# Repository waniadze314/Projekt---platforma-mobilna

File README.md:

# Projekt---platforma-mobilna
Projekt zespołowy

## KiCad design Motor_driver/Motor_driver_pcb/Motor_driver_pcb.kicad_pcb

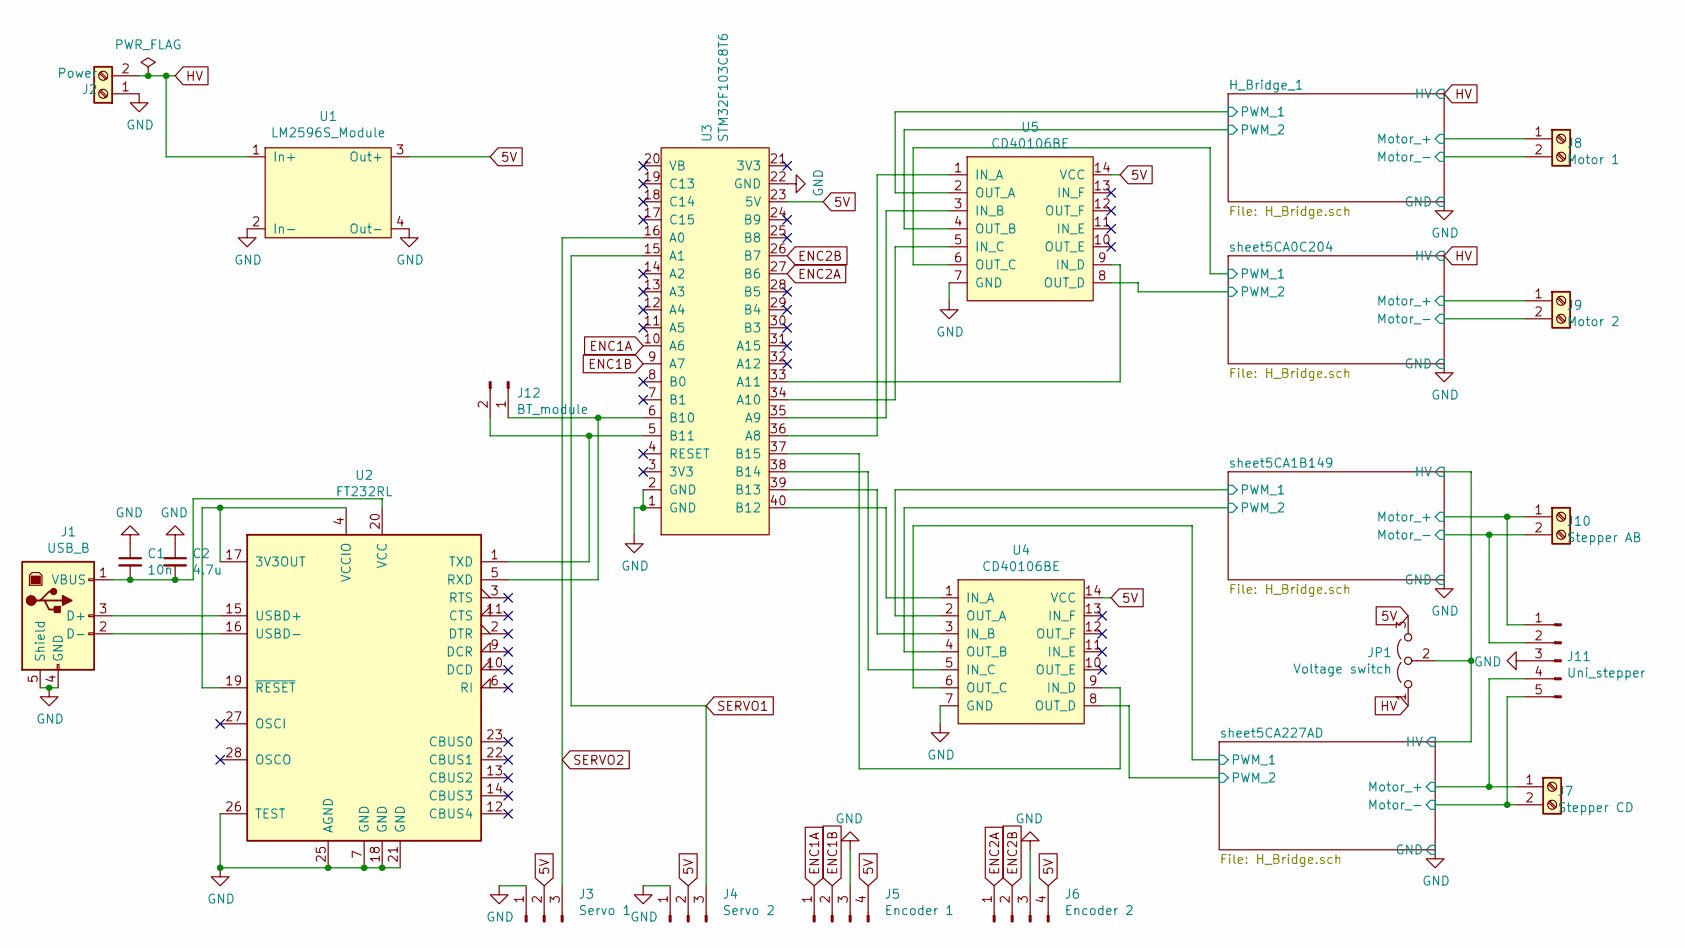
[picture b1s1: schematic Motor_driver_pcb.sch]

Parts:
C1: 10n; C_0805_2012Metric_Pad1.15x1.40mm_HandSolder
C2: 4.7u; CP_Radial_D5.0mm_P2.00mm
J1: USB_B; USB_B_OST_USB-B1HSxx_Horizontal
J2: Power; PinSocket_1x02_P2.54mm_Vertical
J3: Servo 1; PinHeader_1x03_P2.54mm_Vertical
J4: Servo 2; PinHeader_1x03_P2.54mm_Vertical
J5: Encoder 1; PinHeader_1x04_P2.54mm_Vertical
J6: Encoder 2; PinHeader_1x04_P2.54mm_Vertical
J7: Stepper CD; PinSocket_1x02_P2.54mm_Vertical
J8: Motor 1; PinSocket_1x02_P2.54mm_Vertical
J9: Motor 2; PinSocket_1x02_P2.54mm_Vertical
J10: Stepper AB; PinSocket_1x02_P2.54mm_Vertical
J11: Uni_stepper; PinHeader_1x05_P2.54mm_Vertical
J12: BT_module; PinHeader_1x02_P2.54mm_Vertical
JP1: Voltage switch; PinHeader_1x03_P2.54mm_Vertical
U1: LM2596S_Module; LM2596_Module
U2: FT232RL; SSOP-28_5.3x10.2mm_P0.65mm
U3: STM32F103C8T6; STM32F103C8T6_Board
U4, U5: CD40106BE; DIP-14_W7.62mm

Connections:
5V: J3.2, J4.2, J5.4, J6.4, JP1.3 (B), U1.3 (Out+), U3.23 (5V), U4.14 (VCC), U5.14 (VCC)
/H_Bridge_1/Motor_+: J8.1; also elsewhere on the board
/H_Bridge_1/Motor_-: J8.2; also elsewhere on the board
/H_Bridge_1/PWM_1: U5.2 (OUT_A); also elsewhere on the board
/H_Bridge_1/PWM_2: U5.4 (OUT_B); also elsewhere on the board
/sheet5CA0C204/Motor_+: J9.1; also elsewhere on the board
/sheet5CA0C204/Motor_-: J9.2; also elsewhere on the board
/sheet5CA0C204/PWM_1: U5.6 (OUT_C); also elsewhere on the board
/sheet5CA0C204/PWM_2: U5.8 (OUT_D); also elsewhere on the board
/sheet5CA1B149/HV: JP1.2 (C); also elsewhere on the board
/sheet5CA1B149/Motor_+: J10.1, J11.1; also elsewhere on the board
/sheet5CA1B149/Motor_-: J10.2, J11.2; also elsewhere on the board
/sheet5CA1B149/PWM_1: U4.2 (OUT_A); also elsewhere on the board
/sheet5CA1B149/PWM_2: U4.4 (OUT_B); also elsewhere on the board
/sheet5CA227AD/Motor_+: J7.1, J11.4; also elsewhere on the board
/sheet5CA227AD/Motor_-: J7.2, J11.5; also elsewhere on the board
/sheet5CA227AD/PWM_1: U4.6 (OUT_C); also elsewhere on the board
/sheet5CA227AD/PWM_2: U4.8 (OUT_D); also elsewhere on the board
ENC1A: J5.1, U3.10 (A6)
ENC1B: J5.2, U3.9 (A7)
ENC2A: J6.1, U3.27 (B6)
ENC2B: J6.2, U3.26 (B7)
GND: C1.1, C2.1, J1.4 (GND), J1.5 (Shield), J2.1, J3.1, J4.1, J5.3, J6.3, J11.3, U1.2 (In-), U1.4 (Out-), U2.7 (GND), U2.18 (GND), U2.21 (GND), U2.25 (AGND), U2.26 (TEST), U3.1 (GND), U3.2 (GND), U3.22 (GND), U4.7 (GND), U5.7 (GND); also elsewhere on the board
HV: J2.2, JP1.1 (A), U1.1 (In+); also elsewhere on the board
unnamed: C1.2, C2.2, J1.1 (VBUS), U2.20 (VCC)
unnamed: J1.2 (D-), U2.16 (USBD-)
unnamed: J1.3 (D+), U2.15 (USBD+)
unnamed: J12.1, U2.5 (RXD), U3.6 (B10)
unnamed: J12.2, U2.1 (TXD), U3.5 (B11)
unnamed: U2.4 (VCCIO), U2.17 (3V3OUT), U2.19 (~RESET~)
unnamed: U3.33 (A11), U5.9 (IN_D)
unnamed: U3.34 (A10), U5.5 (IN_C)
unnamed: U3.35 (A9), U5.3 (IN_B)
unnamed: U3.36 (A8), U5.1 (IN_A)
unnamed: U3.37 (B15), U4.9 (IN_D)
unnamed: U3.38 (B14), U4.5 (IN_C)
unnamed: U3.39 (B13), U4.3 (IN_B)
unnamed: U3.40 (B12), U4.1 (IN_A)
SERVO1: J4.3, U3.15 (A1)
SERVO2: J3.3, U3.16 (A0)

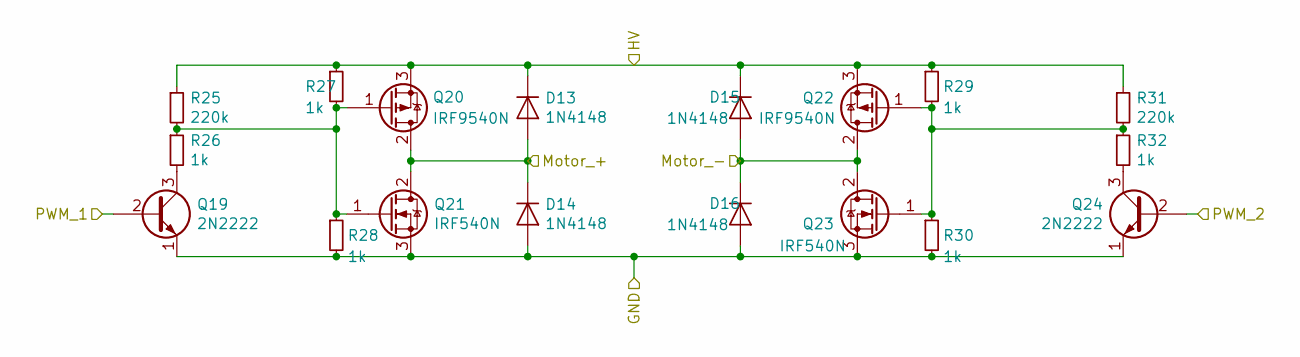
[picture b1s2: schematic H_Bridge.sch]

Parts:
D1, D2, D3, D4: 1N4148; D_DO-35_SOD27_P7.62mm_Horizontal
Q1, Q6: 2N2222; TO-92
Q2, Q4: IRF9540N; TO-220-3_Vertical
Q3, Q5: IRF540N; TO-220-3_Vertical
R1, R7: 220k; R_0805_2012Metric_Pad1.15x1.40mm_HandSolder
R2, R3, R4, R5, R6, R8: 1k; R_0805_2012Metric_Pad1.15x1.40mm_HandSolder

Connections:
/H_Bridge_1/Motor_+: D1.2 (A), D2.1 (K), Q2.2 (D), Q3.2 (D); also elsewhere on the board
/H_Bridge_1/Motor_-: D3.2 (A), D4.1 (K), Q4.2 (D), Q5.2 (D); also elsewhere on the board
/H_Bridge_1/PWM_1: Q1.2 (B); also elsewhere on the board
/H_Bridge_1/PWM_2: Q6.2 (B); also elsewhere on the board
GND: D2.2 (A), D4.2 (A), Q1.1 (E), Q3.3 (S), Q5.3 (S), Q6.1 (E), R4.2, R6.2; also elsewhere on the board
HV: D1.1 (K), D3.1 (K), Q2.3 (S), Q4.3 (S), R1.1, R3.1, R5.1, R7.1; also elsewhere on the board
unnamed: Q1.3 (C), R2.2
unnamed: Q2.1 (G), Q3.1 (G), R1.2, R2.1, R3.2, R4.1
unnamed: Q4.1 (G), Q5.1 (G), R5.2, R6.1, R7.2, R8.1
unnamed: Q6.3 (C), R8.2

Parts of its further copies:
D5, D6, D7, D8, D9, D10, D11, D12, D13, D14, D15, D16: 1N4148; D_DO-35_SOD27_P7.62mm_Horizontal
Q7, Q12, Q13, Q18, Q19, Q24: 2N2222; TO-92
Q8, Q10, Q14, Q16, Q20, Q22: IRF9540N; TO-220-3_Vertical
Q9, Q11, Q15, Q17, Q21, Q23: IRF540N; TO-220-3_Vertical
R9, R15, R17, R23, R25, R31: 220k; R_0805_2012Metric_Pad1.15x1.40mm_HandSolder
R10, R11, R12, R13, R14, R16, R18, R19, R20, R21, R22, R24, R26, R27, R28, R29, R30, R32: 1k; R_0805_2012Metric_Pad1.15x1.40mm_HandSolder

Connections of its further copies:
/sheet5CA0C204/Motor_+: D5.2 (A), D6.1 (K), Q8.2 (D), Q9.2 (D); also elsewhere on the board
/sheet5CA0C204/Motor_-: D7.2 (A), D8.1 (K), Q10.2 (D), Q11.2 (D); also elsewhere on the board
/sheet5CA0C204/PWM_1: Q7.2 (B); also elsewhere on the board
/sheet5CA0C204/PWM_2: Q12.2 (B); also elsewhere on the board
/sheet5CA1B149/HV: D9.1 (K), D11.1 (K), D13.1 (K), D15.1 (K), Q14.3 (S), Q16.3 (S), Q20.3 (S), Q22.3 (S), R17.1, R19.1, R21.1, R23.1, R25.1, R27.1, R29.1, R31.1; also elsewhere on the board
/sheet5CA1B149/Motor_+: D9.2 (A), D10.1 (K), Q14.2 (D), Q15.2 (D); also elsewhere on the board
/sheet5CA1B149/Motor_-: D11.2 (A), D12.1 (K), Q16.2 (D), Q17.2 (D); also elsewhere on the board
/sheet5CA1B149/PWM_1: Q13.2 (B); also elsewhere on the board
/sheet5CA1B149/PWM_2: Q18.2 (B); also elsewhere on the board
/sheet5CA227AD/Motor_+: D13.2 (A), D14.1 (K), Q20.2 (D), Q21.2 (D); also elsewhere on the board
/sheet5CA227AD/Motor_-: D15.2 (A), D16.1 (K), Q22.2 (D), Q23.2 (D); also elsewhere on the board
/sheet5CA227AD/PWM_1: Q19.2 (B); also elsewhere on the board
/sheet5CA227AD/PWM_2: Q24.2 (B); also elsewhere on the board
GND: D6.2 (A), D8.2 (A), D10.2 (A), D12.2 (A), D14.2 (A), D16.2 (A), Q7.1 (E), Q9.3 (S), Q11.3 (S), Q12.1 (E), Q13.1 (E), Q15.3 (S), Q17.3 (S), Q18.1 (E), Q19.1 (E), Q21.3 (S), Q23.3 (S), Q24.1 (E), R12.2, R14.2, R20.2, R22.2, R28.2, R30.2; also elsewhere on the board
HV: D5.1 (K), D7.1 (K), Q8.3 (S), Q10.3 (S), R9.1, R11.1, R13.1, R15.1; also elsewhere on the board
unnamed: Q7.3 (C), R10.2
unnamed: Q8.1 (G), Q9.1 (G), R9.2, R10.1, R11.2, R12.1
unnamed: Q10.1 (G), Q11.1 (G), R13.2, R14.1, R15.2, R16.1
unnamed: Q12.3 (C), R16.2
unnamed: Q13.3 (C), R18.2
unnamed: Q14.1 (G), Q15.1 (G), R17.2, R18.1, R19.2, R20.1
unnamed: Q16.1 (G), Q17.1 (G), R21.2, R22.1, R23.2, R24.1
unnamed: Q18.3 (C), R24.2
unnamed: Q19.3 (C), R26.2
unnamed: Q20.1 (G), Q21.1 (G), R25.2, R26.1, R27.2, R28.1
unnamed: Q22.1 (G), Q23.1 (G), R29.2, R30.1, R31.2, R32.1
unnamed: Q24.3 (C), R32.2

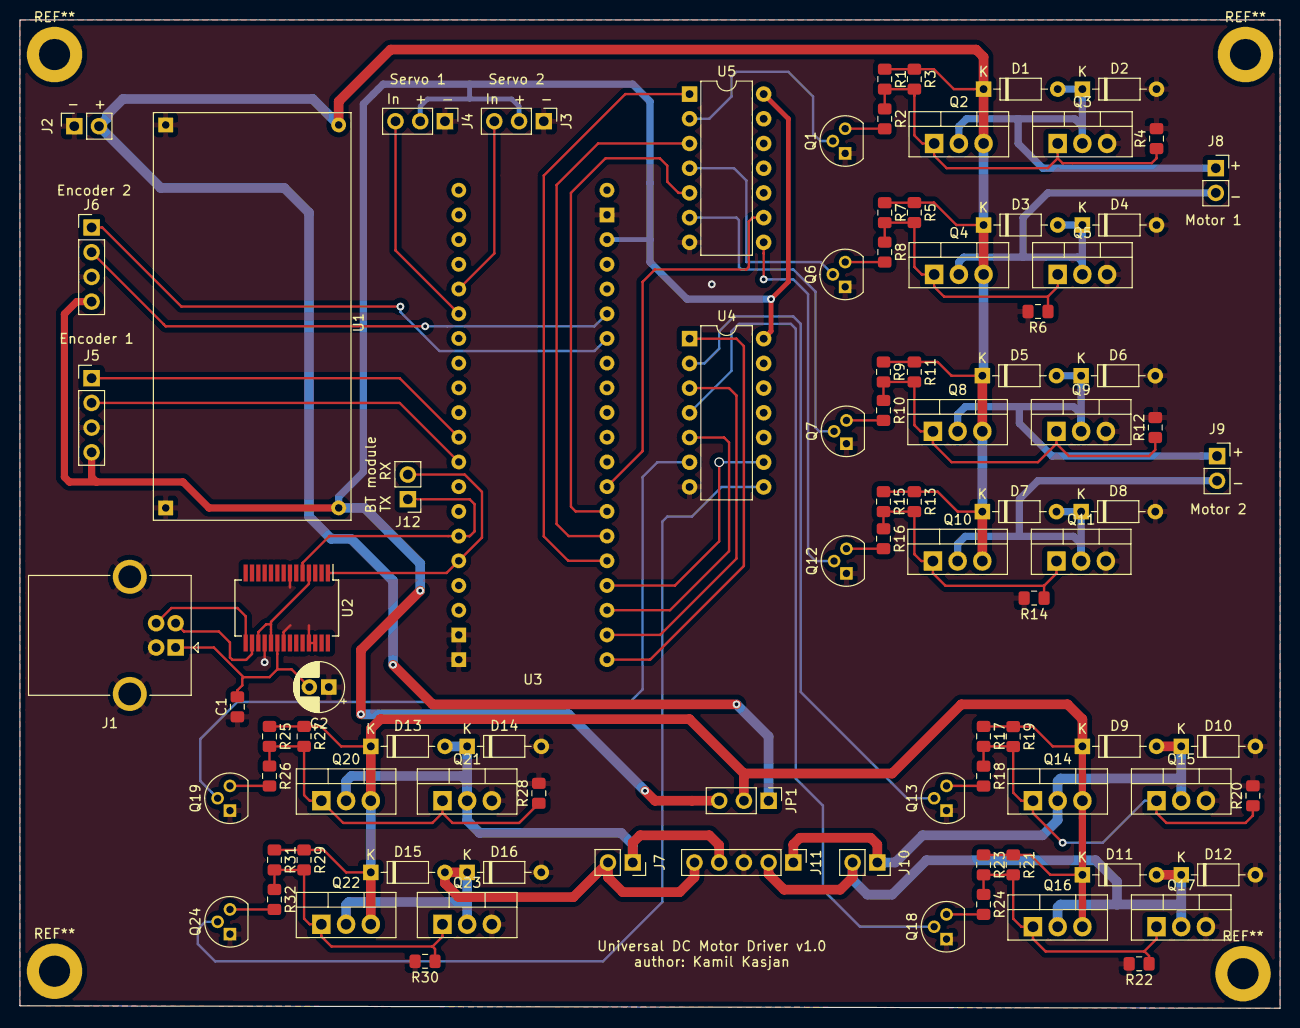
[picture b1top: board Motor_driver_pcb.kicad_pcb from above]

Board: 2 copper layers, 129.5 x 101.6 mm, 92 parts (0 on the bottom side), 56 nets.

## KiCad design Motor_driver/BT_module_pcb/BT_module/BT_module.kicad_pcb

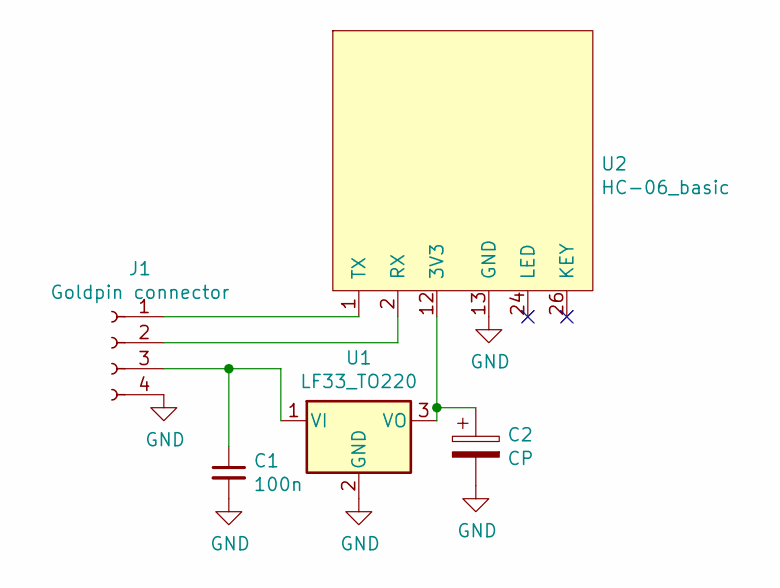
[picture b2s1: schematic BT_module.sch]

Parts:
C1: 100n; C_0805_2012Metric_Pad1.15x1.40mm_HandSolder
C2: CP; CP_Radial_D4.0mm_P2.00mm
J1: Goldpin connector; PinSocket_1x04_P2.54mm_Vertical
U1: LF33_TO220; TO-220-3_Vertical
U2: HC-06_basic; HC-05

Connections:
GND: C1.2, C2.2, J1.4, U1.2 (GND), U2.13 (GND)
unnamed: C1.1, J1.3, U1.1 (VI)
unnamed: C2.1, U1.3 (VO), U2.12 (3V3)
unnamed: J1.1, U2.1 (TX)
unnamed: J1.2, U2.2 (RX)

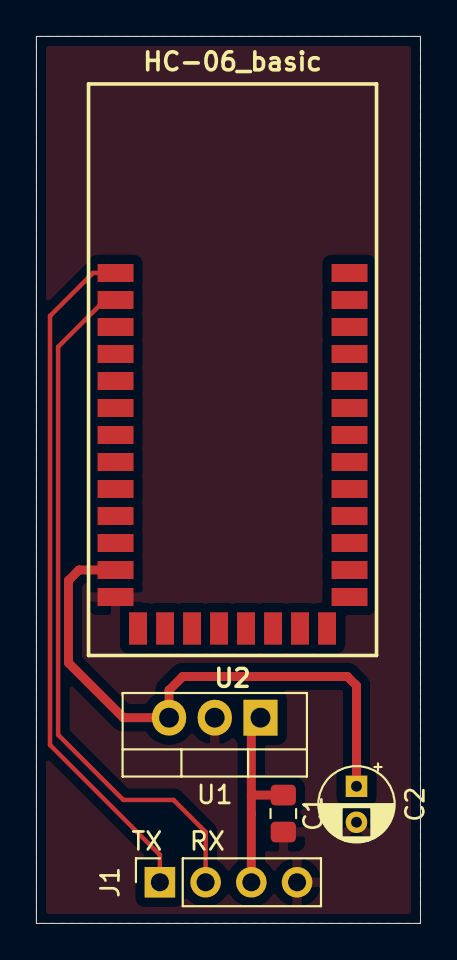
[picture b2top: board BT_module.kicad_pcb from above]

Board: 2 copper layers, 21.3 x 49.3 mm, 5 parts (0 on the bottom side), 5 nets.

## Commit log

2019-03-28 create kicad project
2019-03-28 Init branch
2019-03-28 add electric schema
2019-03-28 update driver schema add uc config
2019-04-04 update schema, create PCB
2019-04-05 finish schema and PCB update uC configuration
2019-04-05 add BT_module PCB add Gerbera files
2019-04-09 create chassis, wheels and motor grips
2019-04-23 Add net
2019-04-26 add final parts and working code
2019-04-26 remove bad project settings
2019-04-28 add velocity measurement
2019-04-28 Add script for image taking
2019-05-03 Add classificator net architecture
2019-05-05 Add Image loading
2019-05-06 modify velocity measurement, upgrade timers settings
2019-05-10 add stepper motor control
2019-05-11 Update image reader
2019-05-11 Add select script
2019-05-11 Update reader
2019-05-11 add turret functionality, fix stepper motor controlling
2019-05-11 add DMA to DC motors controlling
2019-05-13 Update datasets
2019-05-13 Fix loss function
2019-05-14 Update Net
2019-05-19 working speed regulation
2019-05-21 Add template matching recognizer
2019-05-21 Update Recognizer
2019-05-21 Update Canny params
2019-05-22 Update Main
2019-05-29 Update imports
2019-06-01 Add labels
2019-06-10 Final update with tests
